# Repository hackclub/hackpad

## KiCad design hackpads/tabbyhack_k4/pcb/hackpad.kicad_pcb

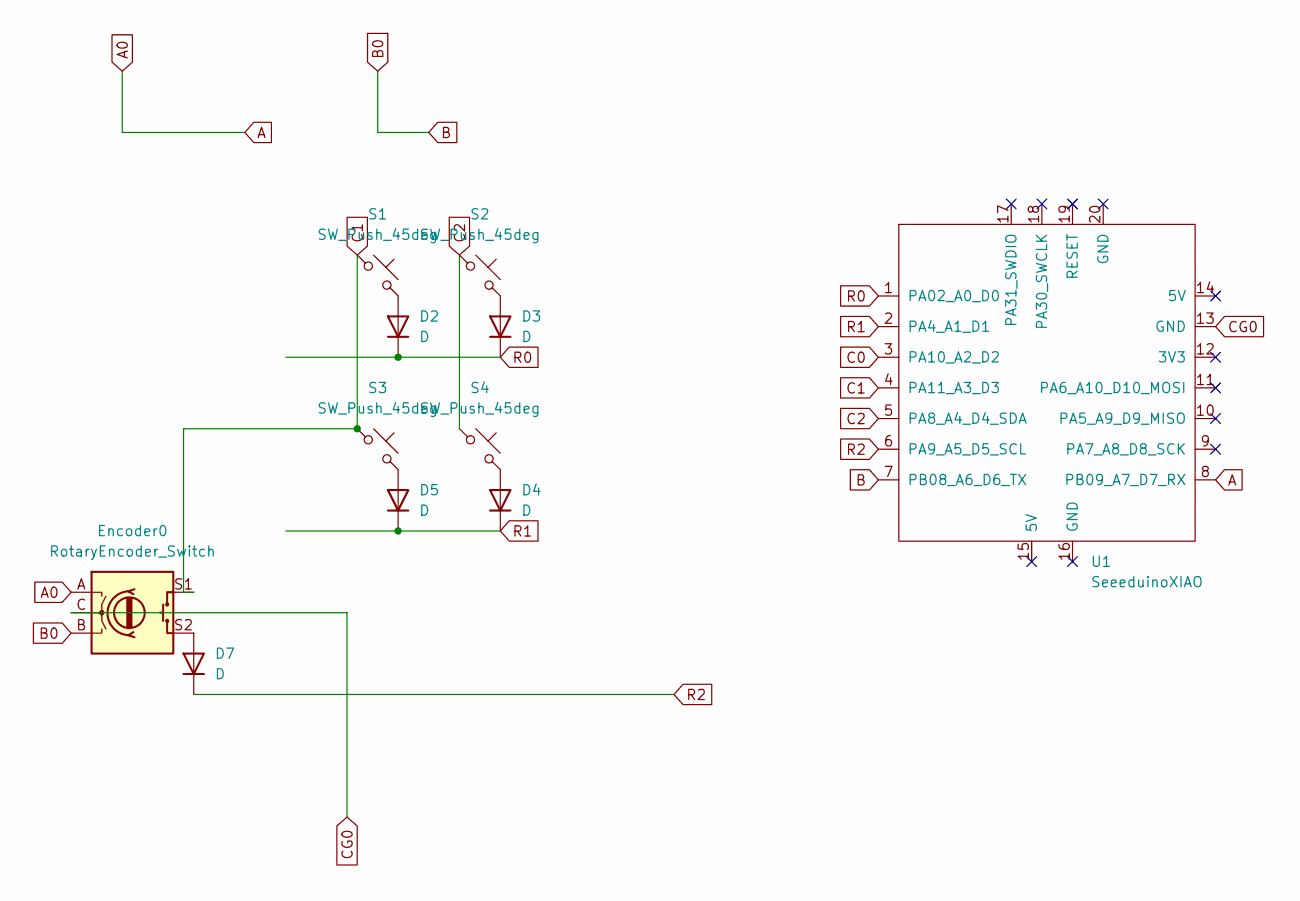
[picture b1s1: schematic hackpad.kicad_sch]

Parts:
D2, D3, D4, D5, D7: D; D_DO-35_SOD27_P7.62mm_Horizontal
Encoder0: RotaryEncoder_Switch; RotaryEncoder_Alps_EC11E-Switch_Vertical_H20mm
S1, S2, S3, S4: SW_Push_45deg; SW_Cherry_MX_1.00u_Plate
U1: SeeeduinoXIAO; XIAO-SAMD21-RP2040-14P-2.54-21X17.8MM (Seeeduino XIAO)

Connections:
A: Encoder0.A, U1.8 (PB09_A7_D7_RX)
B: Encoder0.B, U1.7 (PB08_A6_D6_TX)
C0: U1.3 (PA10_A2_D2)
C1: Encoder0.S1, S1.1, S3.1, U1.4 (PA11_A3_D3)
C2: S2.1, S4.1, U1.5 (PA8_A4_D4_SDA)
CG0: Encoder0.C, U1.13 (GND)
unnamed: D2.2 (A), S1.2
unnamed: D3.2 (A), S2.2
unnamed: D4.2 (A), S4.2
unnamed: D5.2 (A), S3.2
unnamed: D7.2 (A), Encoder0.S2
R0: D2.1 (K), D3.1 (K), U1.1 (PA02_A0_D0)
R1: D4.1 (K), D5.1 (K), U1.2 (PA4_A1_D1)
R2: D7.1 (K), U1.6 (PA9_A5_D5_SCL)

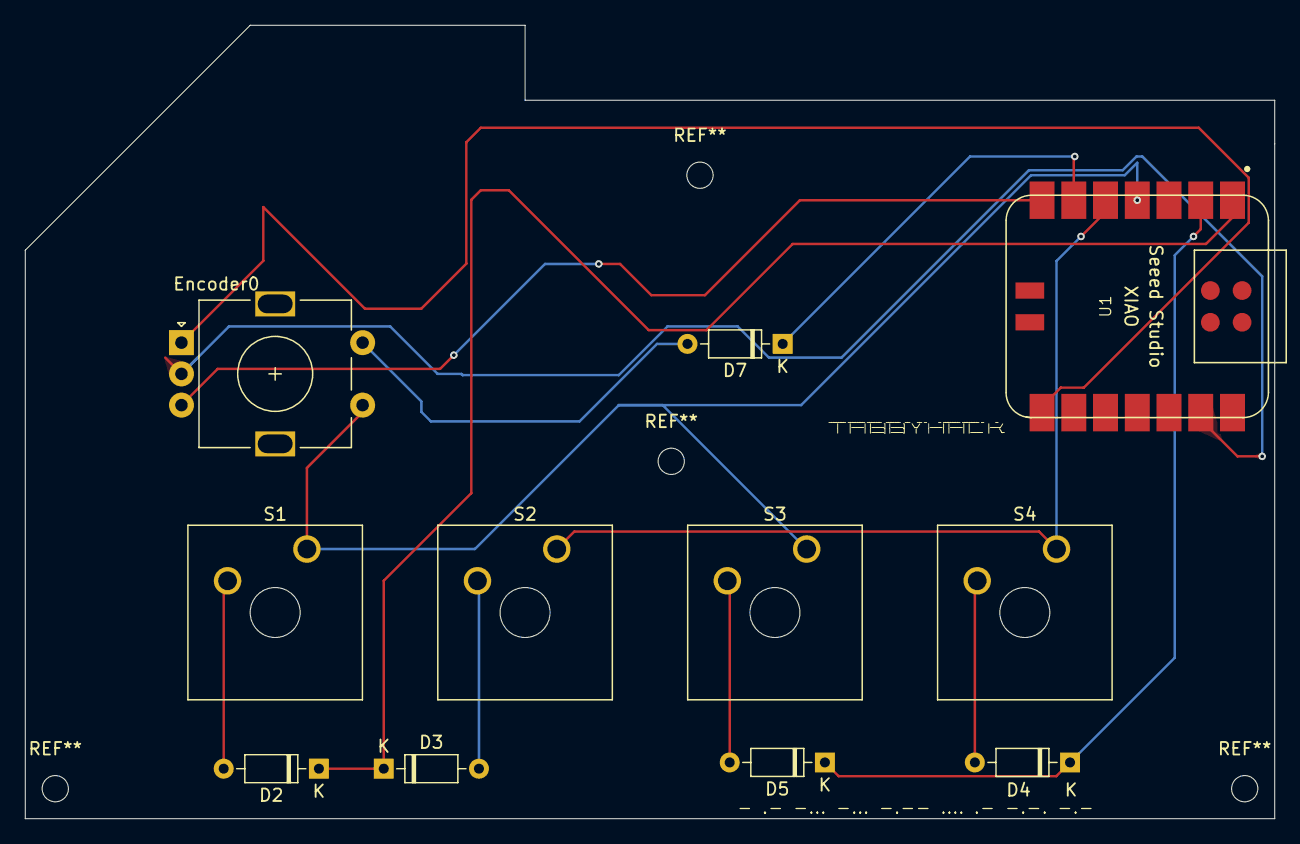
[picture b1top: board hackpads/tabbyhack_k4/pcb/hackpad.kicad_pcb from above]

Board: 2 copper layers, 100.0 x 63.5 mm, 11 parts (0 on the bottom side), 13 nets.

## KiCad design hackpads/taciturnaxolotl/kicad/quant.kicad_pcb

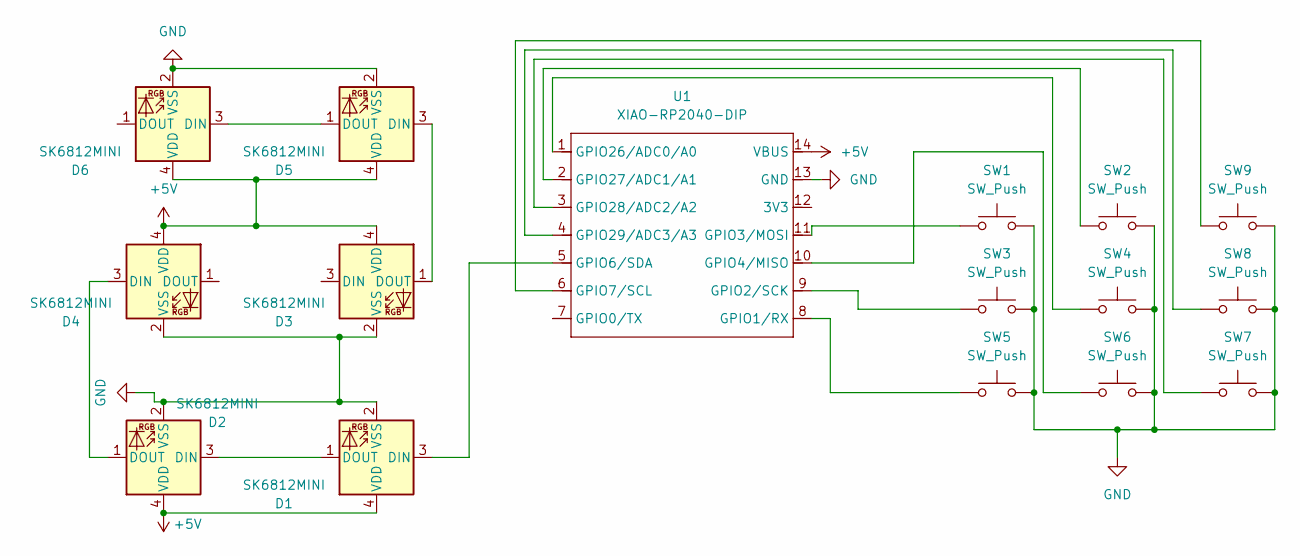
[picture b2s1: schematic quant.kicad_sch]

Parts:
D1, D2, D3, D4, D5, D6: SK6812MINI; LED_SK6812MINI_PLCC4_3.5x3.5mm_P1.75mm
SW1, SW2, SW3, SW4, SW5, SW6, SW7, SW8, SW9: SW_Push; Kailh-PG1353-Solderable-1U
U1: XIAO-RP2040-DIP

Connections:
+5V: D1.4 (VDD), D2.4 (VDD), D3.4 (VDD), D4.4 (VDD), D5.4 (VDD), D6.4 (VDD), U1.14 (VBUS)
GND: D1.2 (VSS), D2.2 (VSS), D3.2 (VSS), D4.2 (VSS), D5.2 (VSS), D6.2 (VSS), SW1.2, SW2.2, SW3.2, SW4.2, SW5.2, SW6.2, SW7.2, SW8.2, SW9.2, U1.13 (GND)
unnamed: D1.3 (DIN), U1.5 (GPIO6/SDA)
unnamed: D1.1 (DOUT), D2.3 (DIN)
unnamed: D2.1 (DOUT), D4.3 (DIN)
unnamed: D3.1 (DOUT), D5.3 (DIN)
unnamed: D5.1 (DOUT), D6.3 (DIN)
unnamed: SW5.1, U1.8 (GPIO1/RX)
unnamed: SW3.1, U1.9 (GPIO2/SCK)
unnamed: SW1.1, U1.11 (GPIO3/MOSI)
unnamed: SW6.1, U1.10 (GPIO4/MISO)
unnamed: SW9.1, U1.6 (GPIO7/SCL)
unnamed: SW4.1, U1.1 (GPIO26/ADC0/A0)
unnamed: SW2.1, U1.2 (GPIO27/ADC1/A1)
unnamed: SW7.1, U1.3 (GPIO28/ADC2/A2)
unnamed: SW8.1, U1.4 (GPIO29/ADC3/A3)

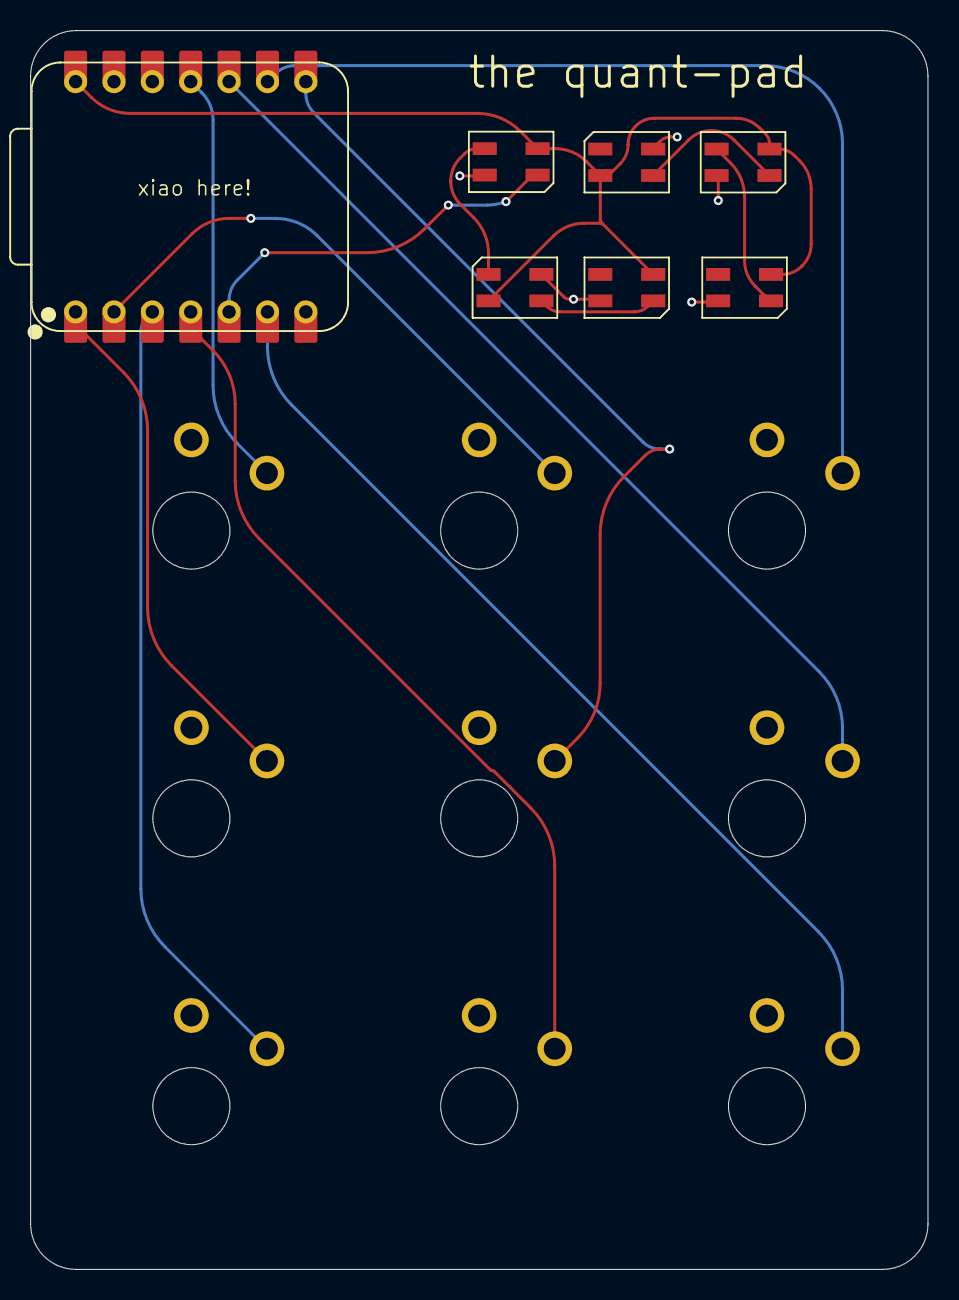
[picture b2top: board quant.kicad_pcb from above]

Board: 2 copper layers, 59.4 x 82.0 mm, 16 parts (0 on the bottom side), 16 nets.

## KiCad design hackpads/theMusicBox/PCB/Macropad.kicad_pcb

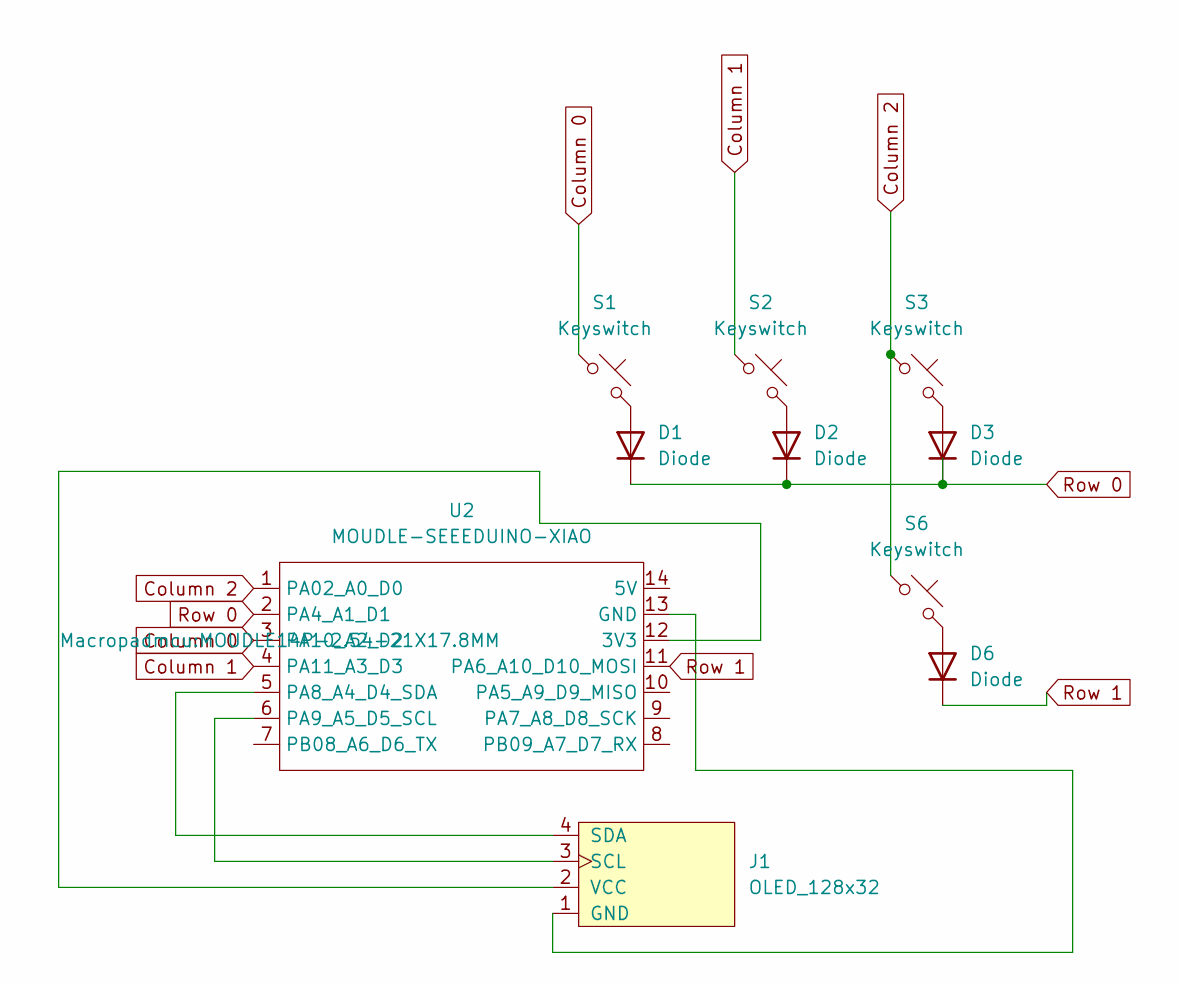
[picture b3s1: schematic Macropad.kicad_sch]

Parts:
D1, D2, D3, D6: Diode; Diode_DO-35
J1: OLED_128x32
S1, S2, S3, S6: Keyswitch; MX_PCB_1.00u
U2: MOUDLE-SEEEDUINO-XIAO; MOUDLE14P-2.54-21X17.8MM

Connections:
Column 0: S1.1, U2.3 (PA10_A2_D2)
Column 1: S2.1, U2.4 (PA11_A3_D3)
Column 2: S3.1, S6.1, U2.1 (PA02_A0_D0)
unnamed: D1.2 (A), S1.2
unnamed: D2.2 (A), S2.2
unnamed: D3.2 (A), S3.2
unnamed: D6.2 (A), S6.2
unnamed: J1.1 (GND), U2.13 (GND)
unnamed: J1.3 (SCL), U2.6 (PA9_A5_D5_SCL)
unnamed: J1.4 (SDA), U2.5 (PA8_A4_D4_SDA)
unnamed: J1.2 (VCC), U2.12 (3V3)
Row 0: D1.1 (K), D2.1 (K), D3.1 (K), U2.2 (PA4_A1_D1)
Row 1: D6.1 (K), U2.11 (PA6_A10_D10_MOSI)

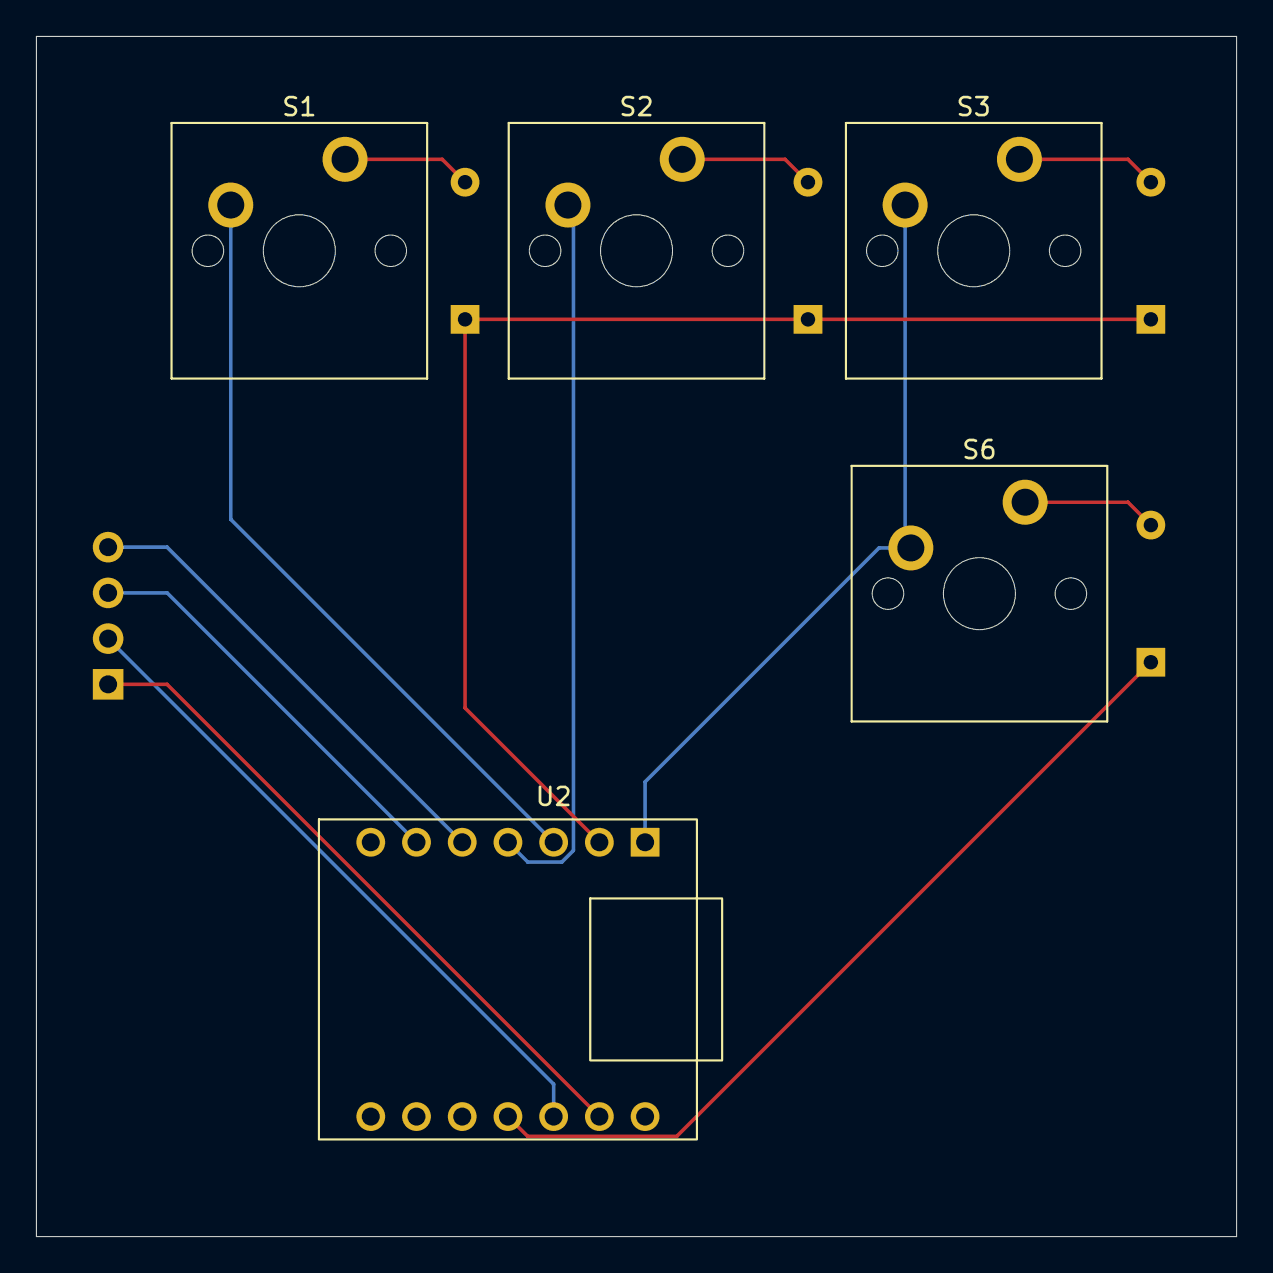
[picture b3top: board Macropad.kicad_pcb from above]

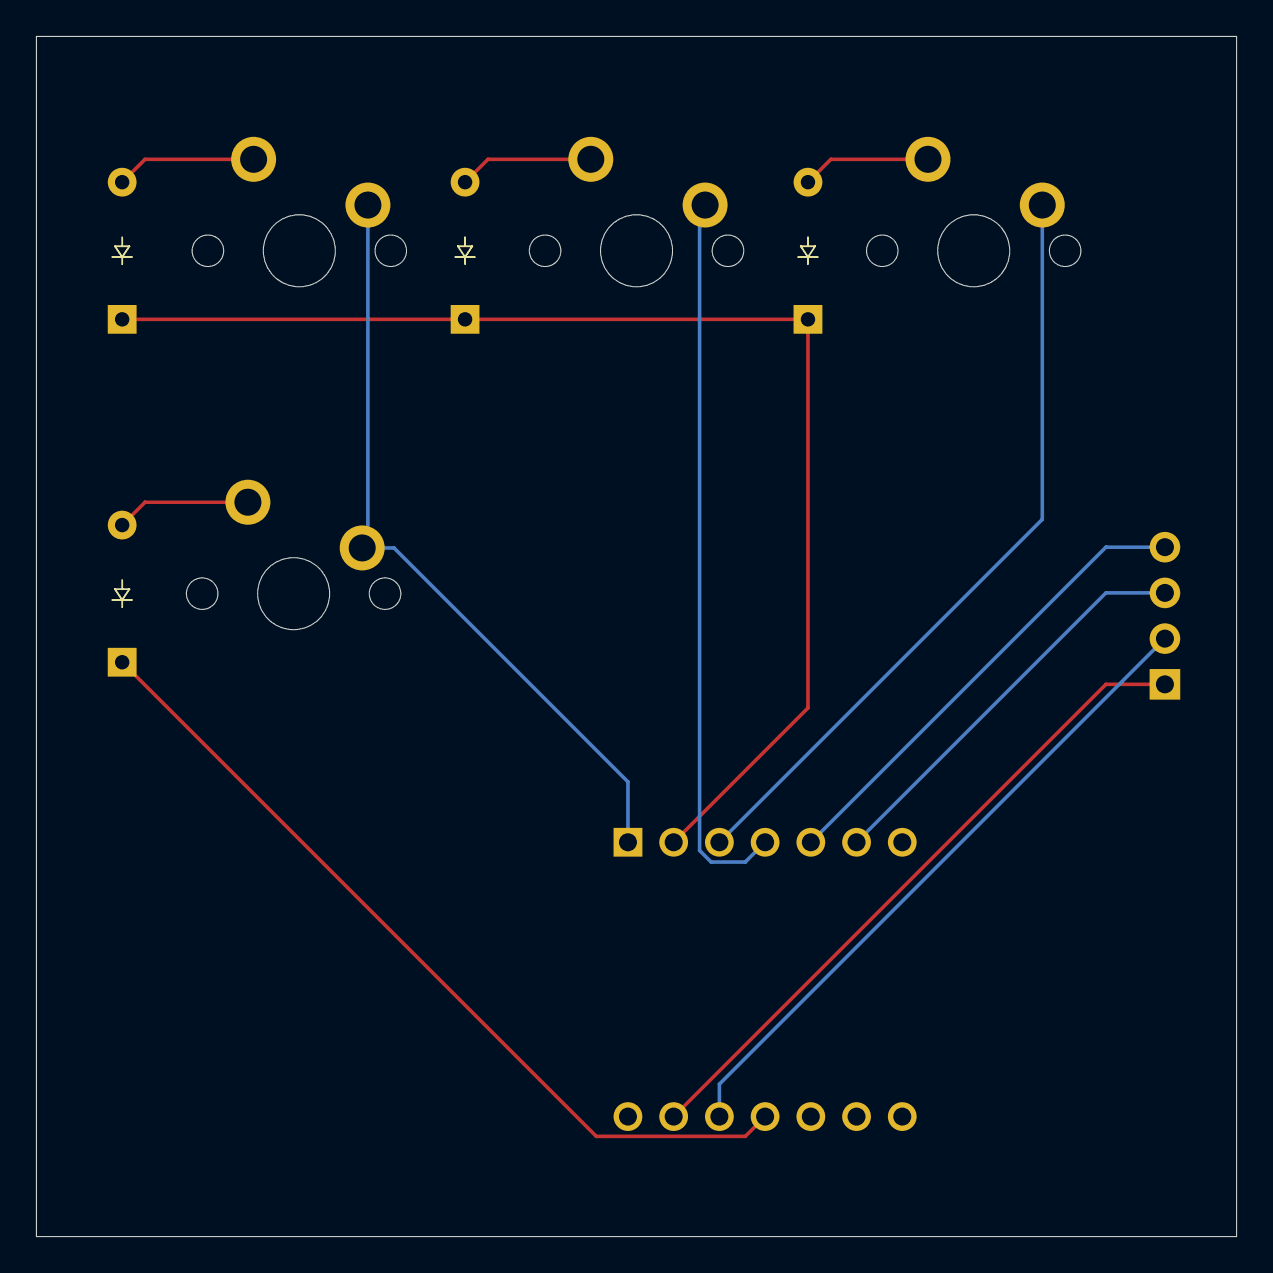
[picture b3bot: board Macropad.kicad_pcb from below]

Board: 2 copper layers, 66.7 x 66.7 mm, 10 parts (4 on the bottom side), 13 nets.

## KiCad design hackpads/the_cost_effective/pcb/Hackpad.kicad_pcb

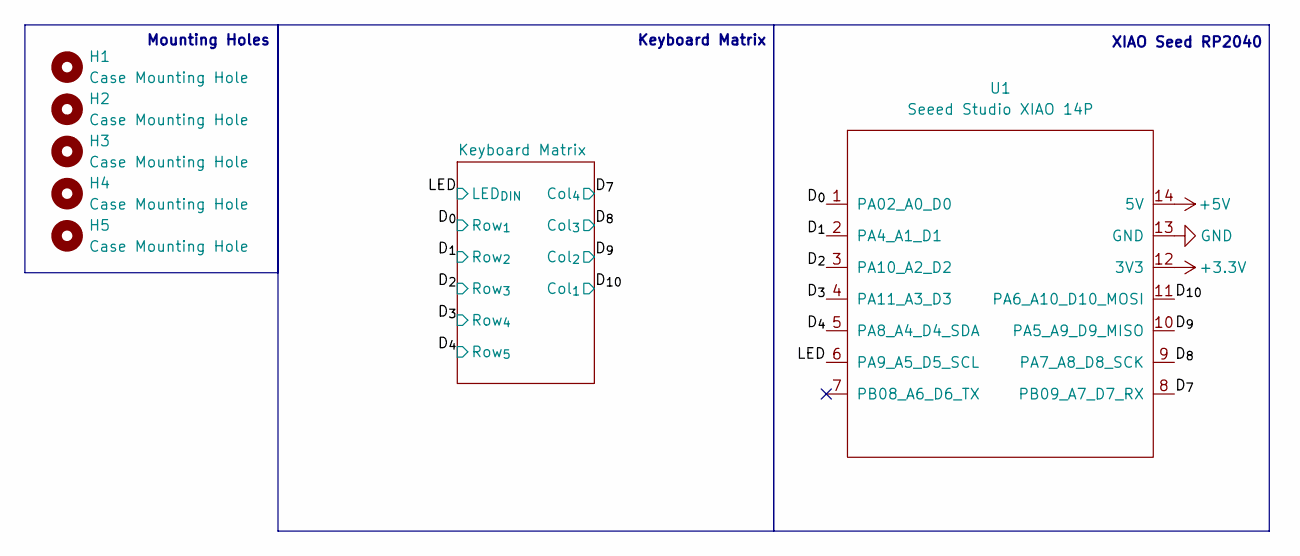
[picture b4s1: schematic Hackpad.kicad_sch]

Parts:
H1, H2, H3, H4, H5: Case Mounting Hole; MountingHole_2mm
U1: Seeed Studio XIAO 14P; XIAO 14P RP2040

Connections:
+3.3V: U1.12 (3V3); also elsewhere on the board
+5V: U1.14 (5V); also elsewhere on the board
/D_{0}: U1.1 (PA02_A0_D0); also elsewhere on the board
/D_{1}: U1.2 (PA4_A1_D1); also elsewhere on the board
/D_{2}: U1.3 (PA10_A2_D2); also elsewhere on the board
/D_{3}: U1.4 (PA11_A3_D3); also elsewhere on the board
/D_{4}: U1.5 (PA8_A4_D4_SDA); also elsewhere on the board
/D_{7}: U1.8 (PB09_A7_D7_RX); also elsewhere on the board
/D_{8}: U1.9 (PA7_A8_D8_SCK); also elsewhere on the board
/D_{9}: U1.10 (PA5_A9_D9_MISO); also elsewhere on the board
/D_{10}: U1.11 (PA6_A10_D10_MOSI); also elsewhere on the board
/LED: U1.6 (PA9_A5_D5_SCL); also elsewhere on the board
GND: U1.13 (GND); also elsewhere on the board

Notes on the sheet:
Keyboard Matrix
Mounting Holes
XIAO Seed RP2040

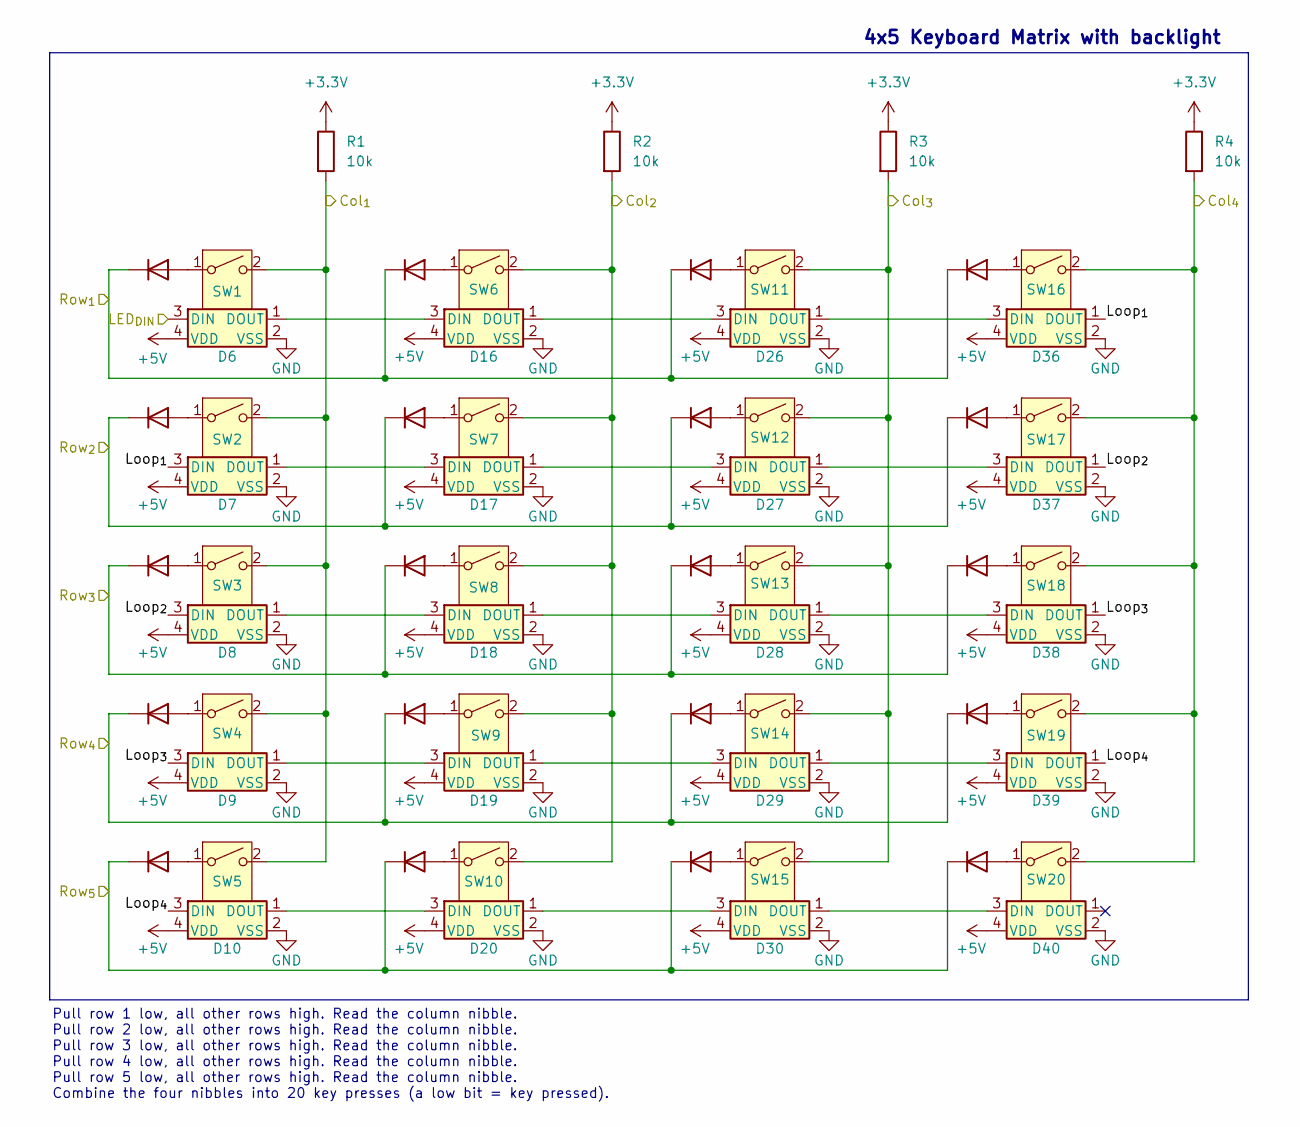
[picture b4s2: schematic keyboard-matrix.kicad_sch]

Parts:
D1, D2, D3, D4, D5, D11, D12, D13, D14, D15, D21, D22, D23, D24, D25, D31, D32, D33, D34, D35: D; D_0402_1005Metric
D6, D7, D8, D9, D10, D16, D17, D18, D19, D20, D26, D27, D28, D29, D30, D36, D37, D38, D39, D40: SK6805; LED_SK6805_PLCC4_2.4x2.7mm_P1.3mm
R1, R2, R3, R4: 10k; R_0402_1005Metric
SW1, SW2, SW3, SW4, SW5, SW6, SW7, SW8, SW9, SW10, SW11, SW12, SW13, SW14, SW15, SW16, SW17, SW18, SW19, SW20: SW_SPST; SW_Hybrid_Cherry_MX_Alps_1.00u

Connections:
+3.3V: R1.1, R2.1, R3.1, R4.1; also elsewhere on the board
+5V: D6.4 (VDD), D7.4 (VDD), D8.4 (VDD), D9.4 (VDD), D10.4 (VDD), D16.4 (VDD), D17.4 (VDD), D18.4 (VDD), D19.4 (VDD), D20.4 (VDD), D26.4 (VDD), D27.4 (VDD), D28.4 (VDD), D29.4 (VDD), D30.4 (VDD), D36.4 (VDD), D37.4 (VDD), D38.4 (VDD), D39.4 (VDD), D40.4 (VDD); also elsewhere on the board
/D_{0}: D1.1 (K), D11.1 (K), D21.1 (K), D31.1 (K); also elsewhere on the board
/D_{1}: D2.1 (K), D12.1 (K), D22.1 (K), D32.1 (K); also elsewhere on the board
/D_{2}: D3.1 (K), D13.1 (K), D23.1 (K), D33.1 (K); also elsewhere on the board
/D_{3}: D4.1 (K), D14.1 (K), D24.1 (K), D34.1 (K); also elsewhere on the board
/D_{4}: D5.1 (K), D15.1 (K), D25.1 (K), D35.1 (K); also elsewhere on the board
/D_{7}: R4.2, SW16.2, SW17.2, SW18.2, SW19.2, SW20.2; also elsewhere on the board
/D_{8}: R3.2, SW11.2, SW12.2, SW13.2, SW14.2, SW15.2; also elsewhere on the board
/D_{9}: R2.2, SW6.2, SW7.2, SW8.2, SW9.2, SW10.2; also elsewhere on the board
/D_{10}: R1.2, SW1.2, SW2.2, SW3.2, SW4.2, SW5.2; also elsewhere on the board
/Keyboard Matrix/Loop_{1}: D7.3 (DIN), D36.1 (DOUT)
/Keyboard Matrix/Loop_{2}: D8.3 (DIN), D37.1 (DOUT)
/Keyboard Matrix/Loop_{3}: D9.3 (DIN), D38.1 (DOUT)
/Keyboard Matrix/Loop_{4}: D10.3 (DIN), D39.1 (DOUT)
/LED: D6.3 (DIN); also elsewhere on the board
GND: D6.2 (VSS), D7.2 (VSS), D8.2 (VSS), D9.2 (VSS), D10.2 (VSS), D16.2 (VSS), D17.2 (VSS), D18.2 (VSS), D19.2 (VSS), D20.2 (VSS), D26.2 (VSS), D27.2 (VSS), D28.2 (VSS), D29.2 (VSS), D30.2 (VSS), D36.2 (VSS), D37.2 (VSS), D38.2 (VSS), D39.2 (VSS), D40.2 (VSS); also elsewhere on the board
unnamed: D1.2 (A), SW1.1
unnamed: D2.2 (A), SW2.1
unnamed: D3.2 (A), SW3.1
unnamed: D4.2 (A), SW4.1
unnamed: D5.2 (A), SW5.1
unnamed: D10.1 (DOUT), D20.3 (DIN)
unnamed: D11.2 (A), SW6.1
unnamed: D12.2 (A), SW7.1
unnamed: D13.2 (A), SW8.1
unnamed: D14.2 (A), SW9.1
unnamed: D15.2 (A), SW10.1
unnamed: D6.1 (DOUT), D16.3 (DIN)
unnamed: D16.1 (DOUT), D26.3 (DIN)
unnamed: D7.1 (DOUT), D17.3 (DIN)
unnamed: D17.1 (DOUT), D27.3 (DIN)
unnamed: D8.1 (DOUT), D18.3 (DIN)
unnamed: D18.1 (DOUT), D28.3 (DIN)
unnamed: D9.1 (DOUT), D19.3 (DIN)
unnamed: D19.1 (DOUT), D29.3 (DIN)
unnamed: D20.1 (DOUT), D30.3 (DIN)
unnamed: D21.2 (A), SW11.1
unnamed: D22.2 (A), SW12.1
unnamed: D23.2 (A), SW13.1
unnamed: D24.2 (A), SW14.1
unnamed: D25.2 (A), SW15.1
unnamed: D26.1 (DOUT), D36.3 (DIN)
unnamed: D27.1 (DOUT), D37.3 (DIN)
unnamed: D28.1 (DOUT), D38.3 (DIN)
unnamed: D29.1 (DOUT), D39.3 (DIN)
unnamed: D30.1 (DOUT), D40.3 (DIN)
unnamed: D31.2 (A), SW16.1
unnamed: D32.2 (A), SW17.1
unnamed: D33.2 (A), SW18.1
unnamed: D34.2 (A), SW19.1
unnamed: D35.2 (A), SW20.1

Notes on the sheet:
Pull row 1 low, all other rows high. Read the column nibble. Pull row 2 low, all other rows high. Read the column nibble. Pull row 3 low, all other rows high. Read the column nibble. Pull row 4 low, all other rows high. Read the column nibble. Pull row 5 low, all other rows high. Read the column ni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
4x5 Keyboard Matrix with backlight

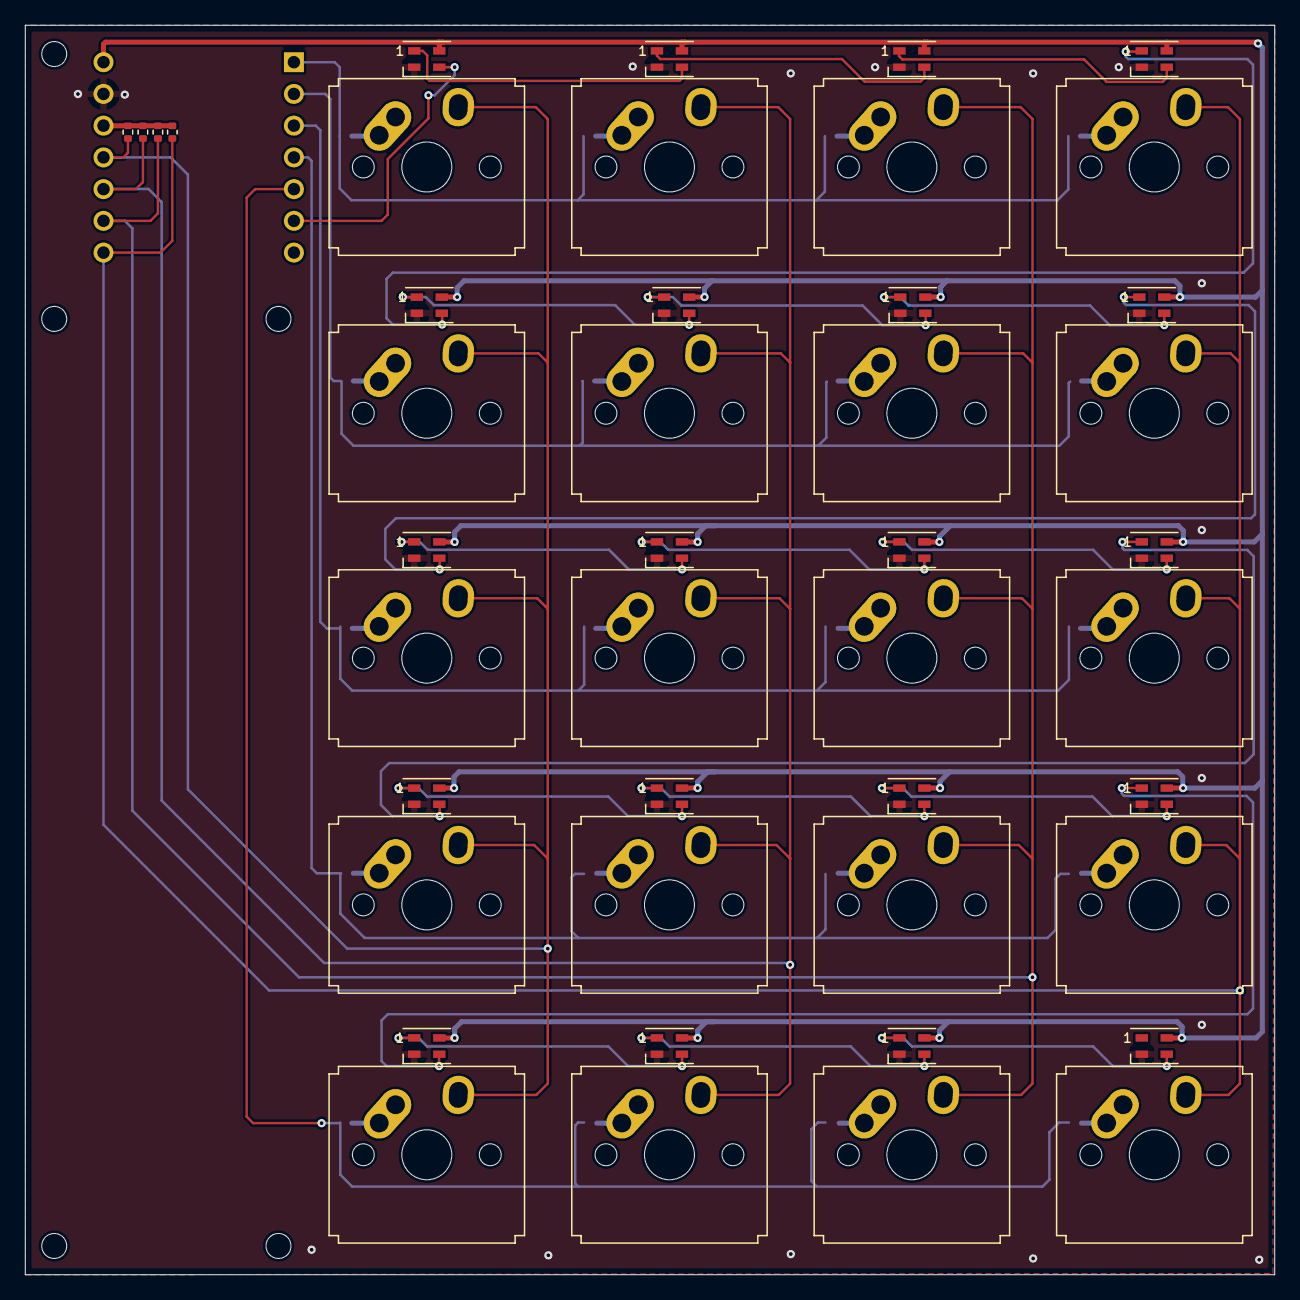
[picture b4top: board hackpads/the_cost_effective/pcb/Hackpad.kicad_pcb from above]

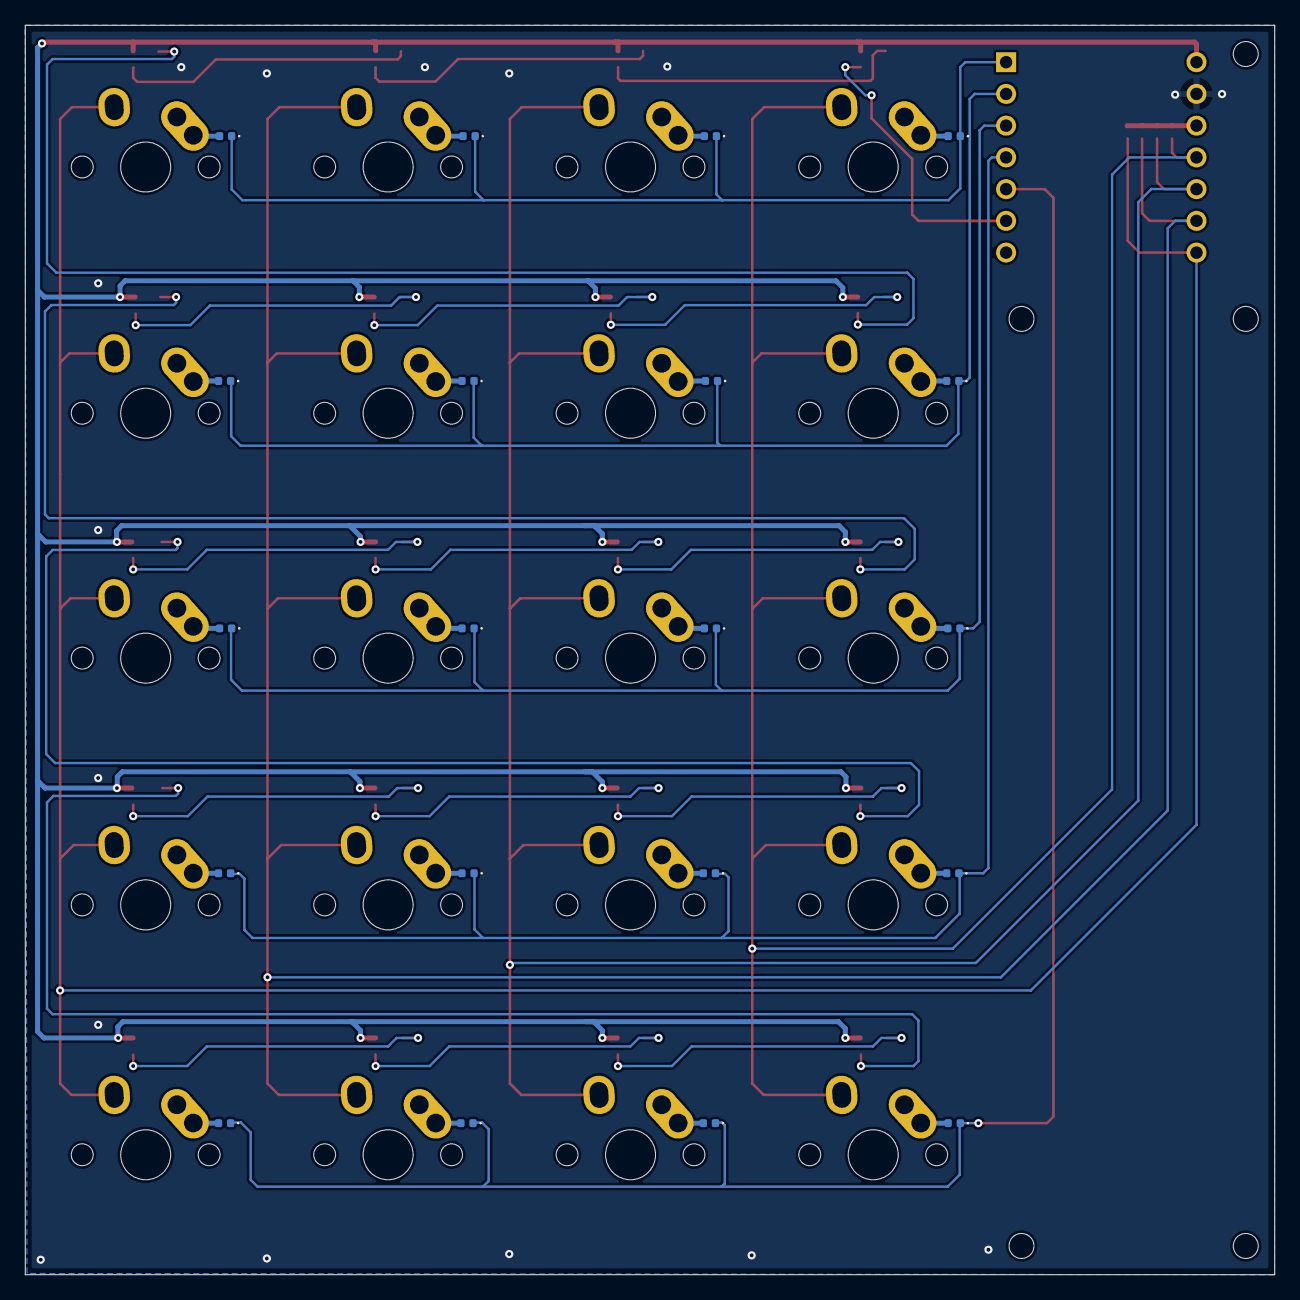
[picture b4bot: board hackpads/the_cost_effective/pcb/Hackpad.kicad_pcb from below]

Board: 2 copper layers, 100.0 x 100.0 mm, 70 parts (21 on the bottom side), 52 nets.

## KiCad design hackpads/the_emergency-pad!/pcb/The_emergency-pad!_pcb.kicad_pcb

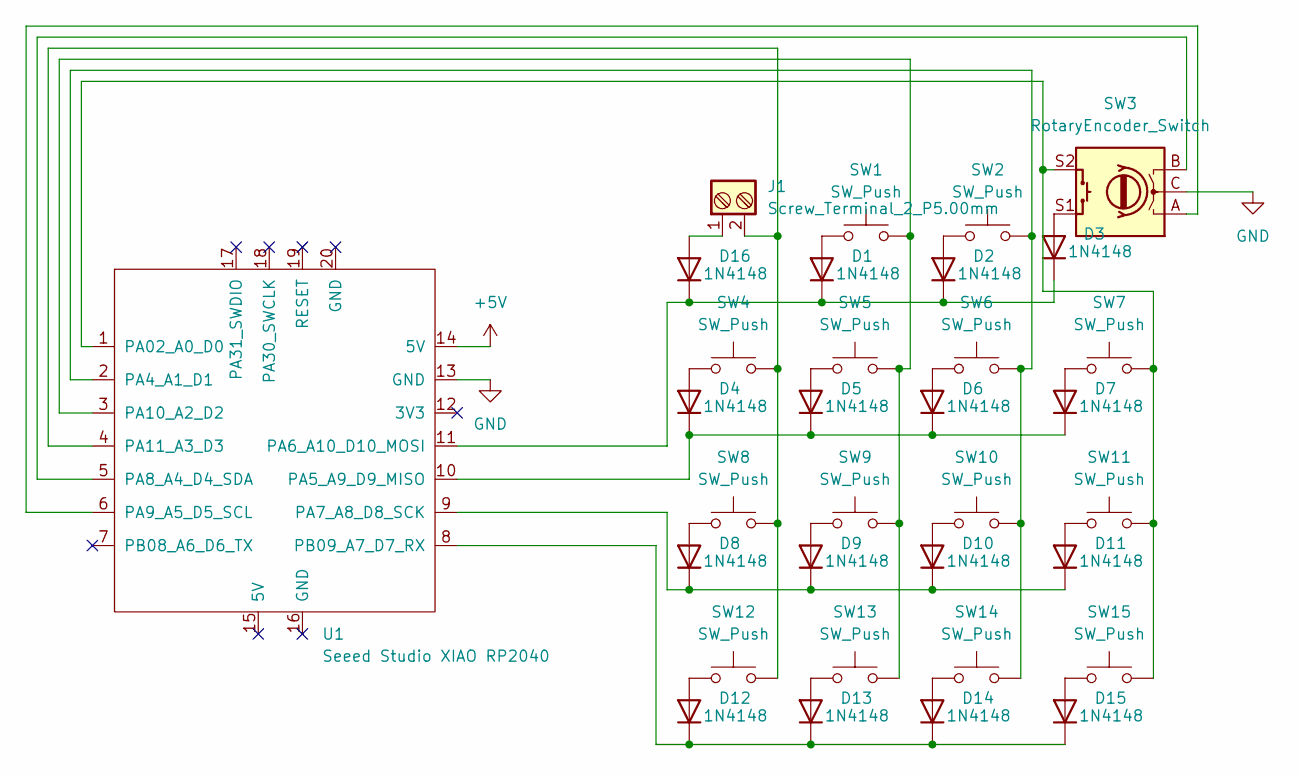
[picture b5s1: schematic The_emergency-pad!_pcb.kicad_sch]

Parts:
D1, D2, D3, D4, D5, D6, D7, D8, D9, D10, D11, D12, D13, D14, D15, D16: 1N4148; D_DO-35_SOD27_P7.62mm_Horizontal
J1: Screw_Terminal_2_P5.00mm; TerminalBlock_Phoenix_PT-1,5-2-5.0-H_1x02_P5.00mm_Horizontal
SW1, SW2, SW4, SW5, SW6, SW7, SW8, SW9, SW10, SW11, SW12, SW13, SW14, SW15: SW_Push; MX-Solderable-1U
SW3: RotaryEncoder_Switch; ec11
U1: Seeed Studio XIAO RP2040; XIAO-RP2040

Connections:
+5V: U1.14 (5V)
GND: SW3.C, U1.13 (GND)
unnamed: D1.2 (A), SW1.2
unnamed: D1.1 (K), D2.1 (K), D3.1 (K), D16.1 (K), U1.11 (PA6_A10_D10_MOSI)
unnamed: D2.2 (A), SW2.2
unnamed: D3.2 (A), SW3.S1
unnamed: D4.2 (A), SW4.2
unnamed: D4.1 (K), D5.1 (K), D6.1 (K), D7.1 (K), U1.10 (PA5_A9_D9_MISO)
unnamed: D5.2 (A), SW5.2
unnamed: D6.2 (A), SW6.2
unnamed: D7.2 (A), SW7.2
unnamed: D8.2 (A), SW8.2
unnamed: D9.2 (A), SW9.2
unnamed: D10.2 (A), SW10.2
unnamed: D8.1 (K), D9.1 (K), D10.1 (K), D11.1 (K), U1.9 (PA7_A8_D8_SCK)
unnamed: D11.2 (A), SW11.2
unnamed: D12.2 (A), SW12.2
unnamed: D12.1 (K), D13.1 (K), D14.1 (K), D15.1 (K), U1.8 (PB09_A7_D7_RX)
unnamed: D13.2 (A), SW13.2
unnamed: D14.2 (A), SW14.2
unnamed: D15.2 (A), SW15.2
unnamed: D16.2 (A), J1.1
unnamed: SW3.S2, SW7.1, SW11.1, SW15.1, U1.1 (PA02_A0_D0)
unnamed: SW2.1, SW6.1, SW10.1, SW14.1, U1.2 (PA4_A1_D1)
unnamed: SW3.B, U1.5 (PA8_A4_D4_SDA)
unnamed: SW3.A, U1.6 (PA9_A5_D5_SCL)
unnamed: SW1.1, SW5.1, SW9.1, SW13.1, U1.3 (PA10_A2_D2)
unnamed: J1.2, SW4.1, SW8.1, SW12.1, U1.4 (PA11_A3_D3)
